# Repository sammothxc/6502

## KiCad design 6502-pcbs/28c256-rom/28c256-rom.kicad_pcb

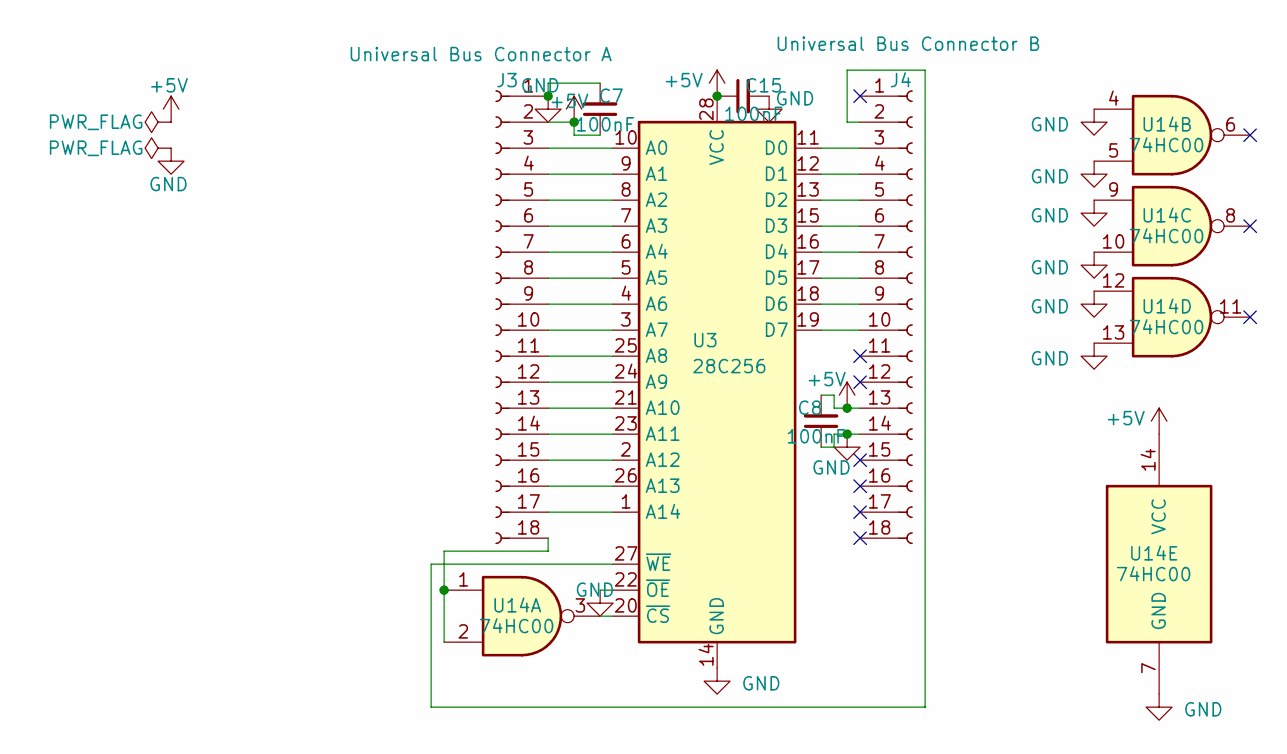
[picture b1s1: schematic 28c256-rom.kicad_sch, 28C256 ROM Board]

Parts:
C7, C8, C15: 100nF; C_Rect_L4.6mm_W2.0mm_P2.50mm_MKS02_FKP02
J3: Universal Bus Connector A; PinSocket_1x18_P2.54mm_Vertical
J4: Universal Bus Connector B; PinSocket_1x18_P2.54mm_Vertical
U3: 28C256; DIP-28_W15.24mm
U14: 74HC00; DIP-14_W7.62mm

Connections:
+5V: C7.1, C8.2, C15.1, J3.2, J4.13, U3.28 (VCC), U14.14 (VCC)
GND: C7.2, C8.1, C15.2, J3.1, J4.14, U3.14 (GND), U3.22 (~OE), U14.4, U14.5, U14.7 (GND), U14.9, U14.10, U14.12, U14.13
unnamed: J3.3, U3.10 (A0)
unnamed: J3.4, U3.9 (A1)
unnamed: J3.5, U3.8 (A2)
unnamed: J3.6, U3.7 (A3)
unnamed: J3.7, U3.6 (A4)
unnamed: J3.8, U3.5 (A5)
unnamed: J3.9, U3.4 (A6)
unnamed: J3.10, U3.3 (A7)
unnamed: J3.11, U3.25 (A8)
unnamed: J3.12, U3.24 (A9)
unnamed: J3.13, U3.21 (A10)
unnamed: J3.14, U3.23 (A11)
unnamed: J3.15, U3.2 (A12)
unnamed: J3.16, U3.26 (A13)
unnamed: J3.17, U3.1 (A14)
unnamed: J3.18, U14.1, U14.2
unnamed: J4.2, U3.27 (~WE)
unnamed: J4.3, U3.11 (D0)
unnamed: J4.4, U3.12 (D1)
unnamed: J4.5, U3.13 (D2)
unnamed: J4.6, U3.15 (D3)
unnamed: J4.7, U3.16 (D4)
unnamed: J4.8, U3.17 (D5)
unnamed: J4.9, U3.18 (D6)
unnamed: J4.10, U3.19 (D7)
unnamed: U3.20 (~CS), U14.3

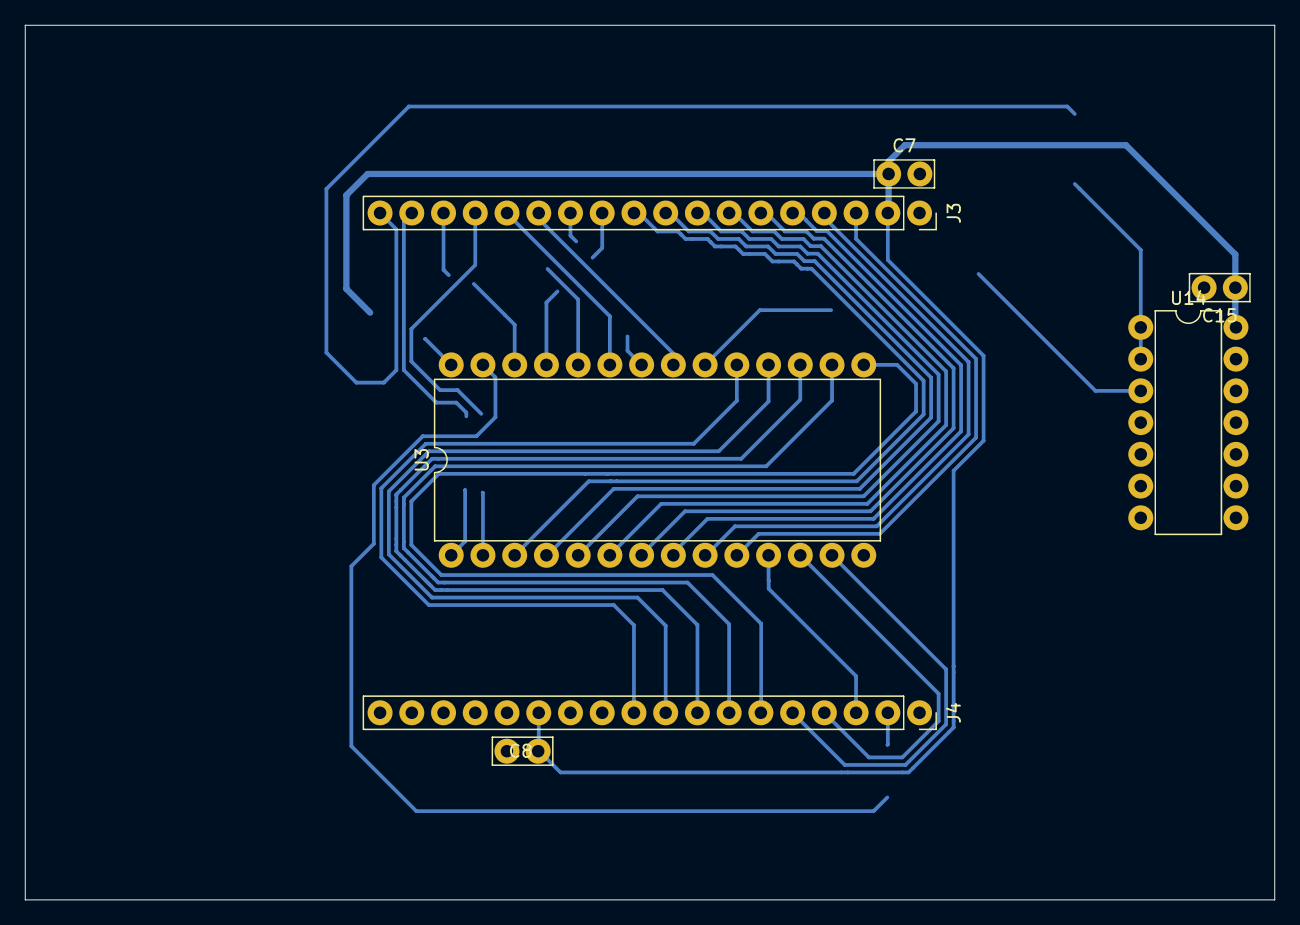
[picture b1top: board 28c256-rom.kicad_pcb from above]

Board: 2 copper layers, 100.0 x 70.0 mm, 7 parts (0 on the bottom side), 28 nets.

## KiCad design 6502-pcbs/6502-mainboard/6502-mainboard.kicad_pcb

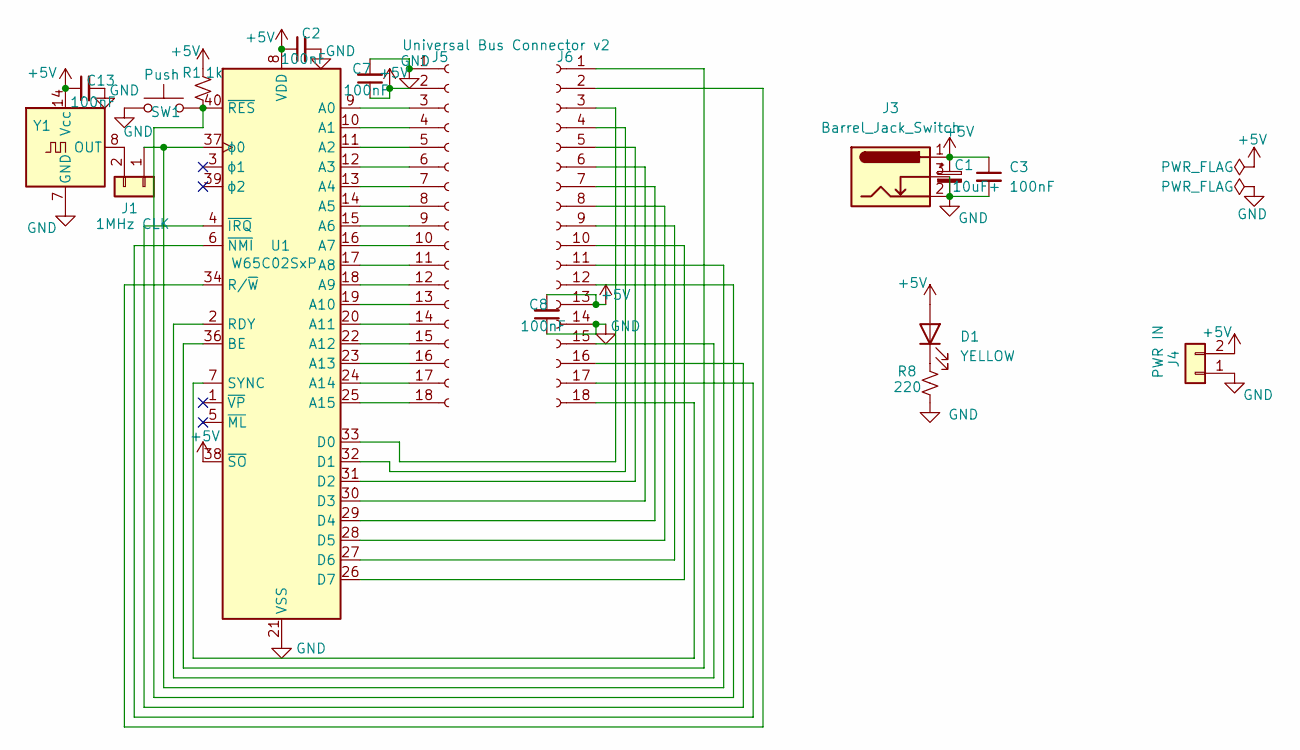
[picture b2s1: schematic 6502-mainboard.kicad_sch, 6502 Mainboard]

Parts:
C1: 10uF+; CP_Radial_D7.5mm_P2.50mm
C2, C3, C7, C8, C13: 100nF; C_Rect_L4.6mm_W2.0mm_P2.50mm_MKS02_FKP02
D1: YELLOW; LED_D5.0mm
J1: 1MHz CLK; PinHeader_1x02_P2.54mm_Vertical
J3: Barrel_Jack_Switch; BarrelJack_Kycon_KLDX-0202-xC_Horizontal
J4: PWR IN; PinSocket_1x02_P2.54mm_Vertical
J5, J6: Universal Bus Connector v2; PinSocket_1x18_P2.54mm_Vertical
R1: 1k; R_Axial_DIN0207_L6.3mm_D2.5mm_P10.16mm_Horizontal
R8: 220; R_Axial_DIN0207_L6.3mm_D2.5mm_P10.16mm_Horizontal
SW1: Push; SW_PUSH_6mm
U1: W65C02SxP; DIP-40_W15.24mm
Y1: ACO-xxxMHz; Oscillator_DIP-14

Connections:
+5V: C1.1, C2.1, C3.1, C7.1, C8.2, C13.1, D1.2 (A), J3.1, J4.2, J5.2, J6.13, R1.1, U1.8 (VDD), U1.38 (~SO), Y1.14 (Vcc)
GND: C1.2, C2.2, C3.2, C7.2, C8.1, C13.2, J3.2, J3.3, J4.1, J5.1, J6.14, R8.2, SW1.1, U1.21 (VSS), Y1.7 (GND)
unnamed: D1.1 (K), R8.1
unnamed: J1.1, J6.11, U1.37 (ϕ0)
unnamed: J1.2, Y1.8 (OUT)
unnamed: J5.3, U1.9 (A0)
unnamed: J5.4, U1.10 (A1)
unnamed: J5.5, U1.11 (A2)
unnamed: J5.6, U1.12 (A3)
unnamed: J5.7, U1.13 (A4)
unnamed: J5.8, U1.14 (A5)
unnamed: J5.9, U1.15 (A6)
unnamed: J5.10, U1.16 (A7)
unnamed: J5.11, U1.17 (A8)
unnamed: J5.12, U1.18 (A9)
unnamed: J5.13, U1.19 (A10)
unnamed: J5.14, U1.20 (A11)
unnamed: J5.15, U1.22 (A12)
unnamed: J5.16, U1.23 (A13)
unnamed: J5.17, U1.24 (A14)
unnamed: J5.18, U1.25 (A15)
unnamed: J6.1, U1.36 (BE)
unnamed: J6.2, U1.34 (R/~W)
unnamed: J6.3, U1.33 (D0)
unnamed: J6.4, U1.32 (D1)
unnamed: J6.5, U1.31 (D2)
unnamed: J6.6, U1.30 (D3)
unnamed: J6.7, U1.29 (D4)
unnamed: J6.8, U1.28 (D5)
unnamed: J6.9, U1.27 (D6)
unnamed: J6.10, U1.26 (D7)
unnamed: J6.12, R1.2, SW1.2, U1.40 (~RES)
unnamed: J6.15, U1.2 (RDY)
unnamed: J6.16, U1.4 (~IRQ)
unnamed: J6.17, U1.6 (~NMI)
unnamed: J6.18, U1.7 (SYNC)

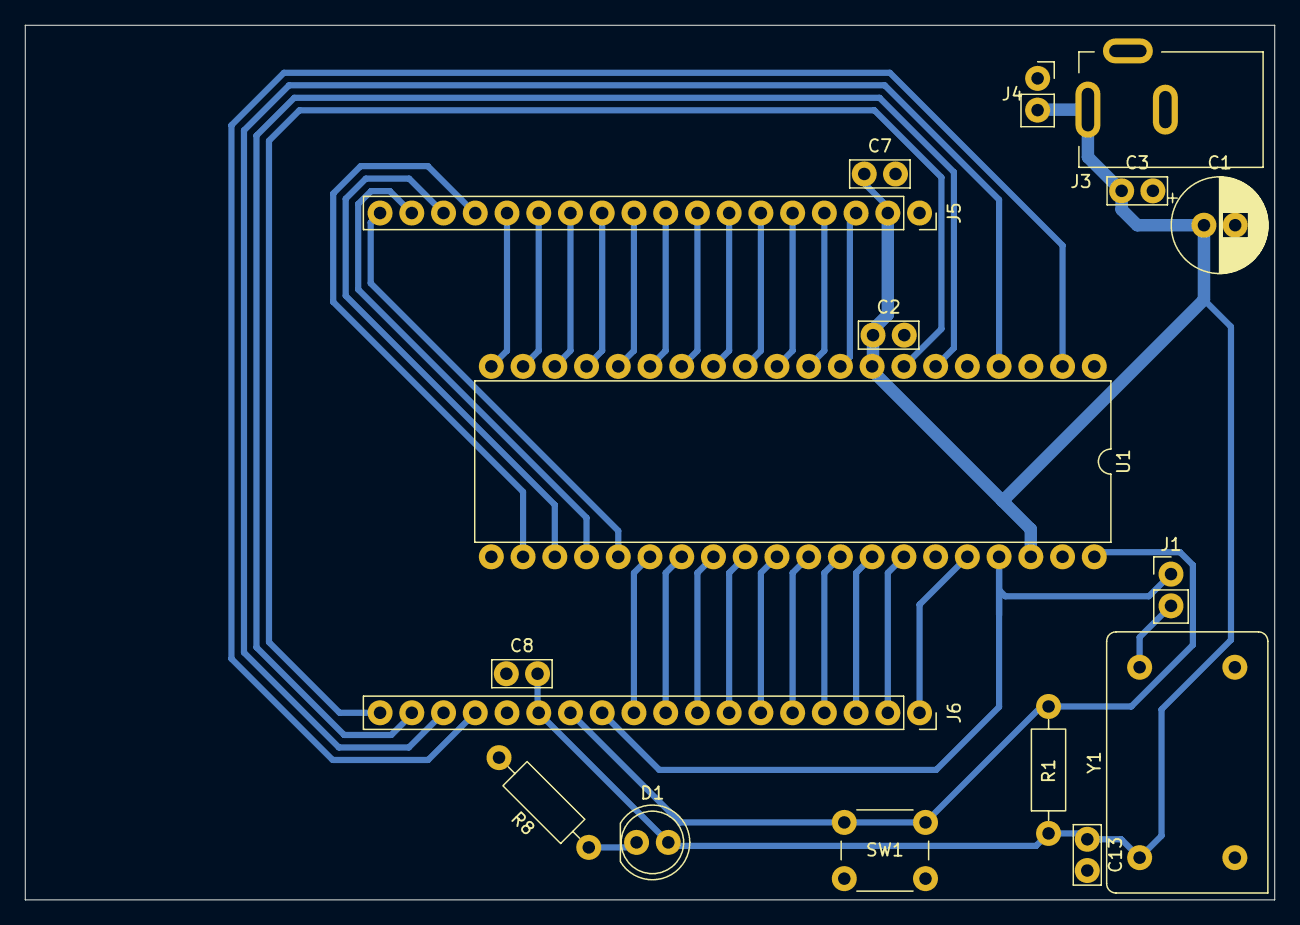
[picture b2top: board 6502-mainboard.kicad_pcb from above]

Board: 2 copper layers, 100.0 x 70.0 mm, 17 parts (0 on the bottom side), 36 nets.

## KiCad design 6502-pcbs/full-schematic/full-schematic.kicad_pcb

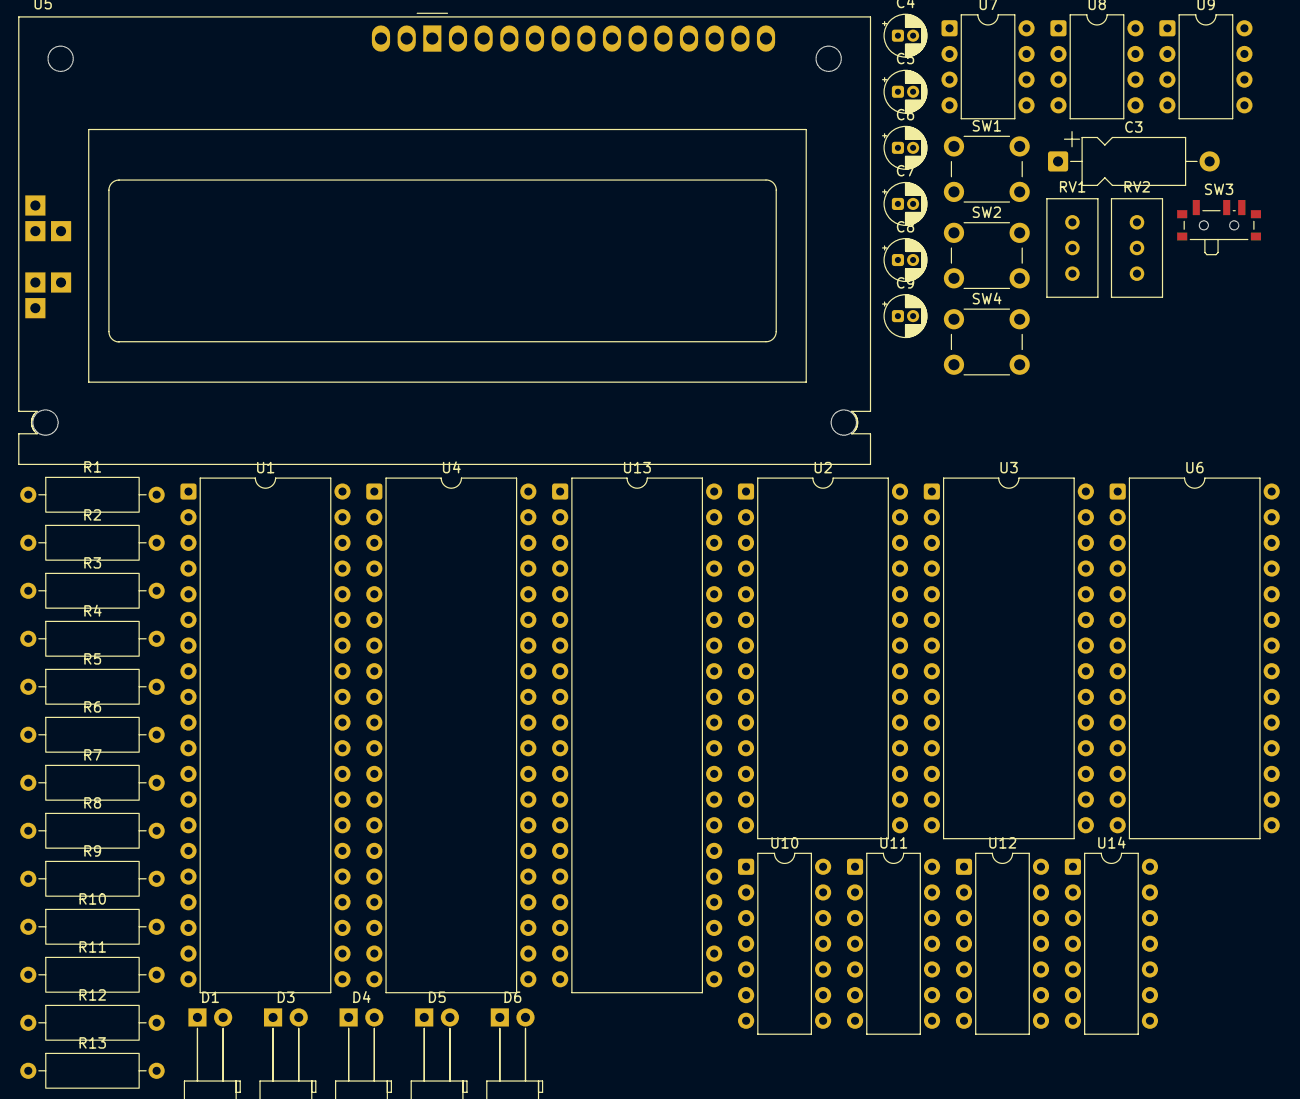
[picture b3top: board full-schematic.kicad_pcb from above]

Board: 2 copper layers, 45 parts (0 on the bottom side), 67 nets, no tracks yet.

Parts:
C3: 1uF; CP_Axial_L10.0mm_D4.5mm_P15.00mm_Horizontal
C4, C5, C8: 0.1uF; CP_Radial_D4.0mm_P1.50mm
C6, C7, C9: 0.01uF; CP_Radial_D4.0mm_P1.50mm
D1: RED; LED_D5.0mm_Horizontal_O6.35mm_Z9.0mm
D3, D4, D5, D6: YELLOW; LED_D5.0mm_Horizontal_O6.35mm_Z9.0mm
R1, R2, R3, R5, R6, R7, R12: 1k; R_Axial_DIN0309_L9.0mm_D3.2mm_P12.70mm_Horizontal
R4: 1M; R_Axial_DIN0309_L9.0mm_D3.2mm_P12.70mm_Horizontal
R8, R9, R10, R11, R13: 220; R_Axial_DIN0309_L9.0mm_D3.2mm_P12.70mm_Horizontal
RV1: 10k?; Potentiometer_Bourns_3386C_Horizontal
RV2: 1M; Potentiometer_Bourns_3386C_Horizontal
SW1, SW2, SW4: Push; SW_PUSH_6mm
SW3: SW_SPDT; SW_SPDT_PCM12
U1: W65C02SxP; DIP-40_W15.24mm
U2: HM62256BLP; DIP-28_W15.24mm
U3: 28C256; DIP-28_W15.24mm
U4: W65C22SxP; DIP-40_W15.24mm
U5: RC1602A
U6: W65C51NxP; DIP-28_W15.24mm
U7, U8, U9: NE555P; DIP-8_W7.62mm
U10: 74LS08; DIP-14_W7.62mm
U11: 74LS04; DIP-14_W7.62mm
U12: 74LS32; DIP-14_W7.62mm
U13: ATmega644-20P; DIP-40_W15.24mm
U14: 74HC00; DIP-14_W7.62mm

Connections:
+5V: C4.1, C5.1, R1.1, R2.1, R4.1, R5.1, R6.1, R7.1, R12.1, U1.2 (RDY), U1.4 (~IRQ), U1.6 (~NMI), U1.8 (VDD), U1.36 (BE), U1.38 (~SO), U2.28 (VCC), U3.27 (~WE), U3.28 (VCC), U4.20 (VCC), U5.2 (VDD), U5.15 (A/VEE), U7.4 (R), U7.8 (VCC), U8.4 (R), U8.8 (VCC), U9.8 (VCC), U13.10 (VCC), U13.30 (AVCC)
/HALT: D6.2 (A), U11.3, U13.14 (PD0)
GND: C3.2, C4.2, C5.2, C6.2, C7.2, C8.2, C9.2, R8.2, R9.2, R10.2, R11.2, R13.2, RV1.3, SW1.1, SW2.1, SW4.1, U1.21 (VSS), U2.14 (GND), U3.14 (GND), U3.22 (~OE), U4.1 (VSS), U5.1 (VSS), U5.16 (K), U6.1 (VSS_1), U7.1 (GND), U8.1 (GND), U9.1 (GND), U9.6 (THR), U13.11 (GND), U13.31 (GND)
unnamed: D1.2 (A), U1.37 (ϕ0), U10.8, U11.5, U13.16 (PD2)
unnamed: D1.1 (K), R8.1
unnamed: D3.2 (A), U8.3 (Q), U10.5
unnamed: D3.1 (K), R9.1
unnamed: D4.2 (A), U7.3 (Q), U10.1
unnamed: D4.1 (K), R10.1
unnamed: D5.2 (A), U9.3 (Q), U10.2, U11.1
unnamed: D5.1 (K), R11.1
unnamed: D6.1 (K), R13.1
unnamed: R3.2, RV2.2
unnamed: R6.2, SW3.1 (A), U9.2 (TR)
unnamed: R7.2, SW3.3 (C), U9.4 (R)
unnamed: U1.9 (A0), U2.10 (A0), U3.10 (A0), U13.40 (PA0)
unnamed: U1.10 (A1), U2.9 (A1), U3.9 (A1), U13.39 (PA1)
unnamed: U1.11 (A2), U2.8 (A2), U3.8 (A2), U13.38 (PA2)
unnamed: U1.12 (A3), U2.7 (A3), U3.7 (A3), U13.37 (PA3)
unnamed: U1.13 (A4), U2.6 (A4), U3.6 (A4), U13.36 (PA4)
unnamed: U1.14 (A5), U2.5 (A5), U3.5 (A5), U13.35 (PA5)
unnamed: U1.15 (A6), U2.4 (A6), U3.4 (A6), U13.34 (PA6)
unnamed: U1.16 (A7), U2.3 (A7), U3.3 (A7), U13.33 (PA7)
unnamed: U1.17 (A8), U2.25 (A8), U3.25 (A8), U13.1 (PB0)
unnamed: U1.18 (A9), U2.24 (A9), U3.24 (A9), U13.2 (PB1)
unnamed: U1.19 (A10), U2.21 (A10), U3.21 (A10), U13.3 (PB2)
unnamed: U1.20 (A11), U2.23 (A11), U3.23 (A11), U13.4 (PB3)
unnamed: U1.22 (A12), U2.2 (A12), U3.2 (A12), U13.5 (PB4)
unnamed: U1.23 (A13), U2.26 (A13), U3.26 (A13), U13.6 (PB5)
unnamed: U1.24 (A14), U2.1 (A14), U3.1 (A14), U13.7 (PB6)
unnamed: U1.25 (A15), U13.8 (PB7), U14.1, U14.2
unnamed: U1.33 (D0), U2.11 (Q0), U3.11 (D0), U4.33 (D0), U13.22 (PC0)
unnamed: U1.32 (D1), U2.12 (Q1), U3.12 (D1), U4.32 (D1), U13.23 (PC1)
unnamed: U1.31 (D2), U2.13 (Q2), U3.13 (D2), U4.31 (D2), U13.24 (PC2)
unnamed: U1.30 (D3), U2.15 (Q3), U3.15 (D3), U4.30 (D3), U13.25 (PC3)
unnamed: U1.29 (D4), U2.16 (Q4), U3.16 (D4), U4.29 (D4), U13.26 (PC4)
unnamed: U1.28 (D5), U2.17 (Q5), U3.17 (D5), U4.28 (D5), U13.27 (PC5)
unnamed: U1.27 (D6), U2.18 (Q6), U3.18 (D6), U4.27 (D6), U13.28 (PC6)
unnamed: U1.26 (D7), U2.19 (Q7), U3.19 (D7), U4.26 (D7), U13.29 (PC7)
unnamed: U1.34 (R/~W), U13.15 (PD1)
unnamed: R1.2, SW1.2, U1.40 (~RES)
unnamed: U3.20 (~CS), U14.3
unnamed: U4.7 (PA5), U5.4 (RS)
unnamed: U4.8 (PA6), U5.5 (R/W)
unnamed: U4.9 (PA7), U5.6 (E)
unnamed: U4.10 (PB0), U5.7 (DB0)
unnamed: U4.11 (PB1), U5.8 (DB1)
unnamed: U4.12 (PB2), U5.9 (DB2)
unnamed: U4.13 (PB3), U5.10 (DB3)
unnamed: U4.14 (PB4), U5.11 (DB4)
unnamed: U4.15 (PB5), U5.12 (DB5)
unnamed: U4.16 (PB6), U5.13 (DB6)
unnamed: U4.17 (PB7), U5.14 (DB7)
unnamed: RV1.2, U5.3 (VO)
unnamed: C6.1, U7.5 (CV)
unnamed: R2.2, R3.1, U7.7 (DIS)
unnamed: C3.1, RV2.3, U7.2 (TR), U7.6 (THR)
unnamed: C7.1, U8.5 (CV)
unnamed: C8.1, R4.2, U8.6 (THR), U8.7 (DIS)
unnamed: R5.2, SW2.2, U8.2 (TR)
unnamed: C9.1, U9.5 (CV)
unnamed: U10.3, U12.1
unnamed: U10.4, U11.2
unnamed: U10.6, U12.2
unnamed: U10.9, U12.3
unnamed: U10.10, U11.4
unnamed: R12.2, SW4.2, U13.9 (~RESET)

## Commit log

2025-07-14 makerom.py
2025-07-14 flashrom.py, and eeprom programmer stuff
2025-07-14 flashrom work
2025-07-14 arduino prorgammer
2025-07-15 mega2560
2025-08-01 msbasic
2025-08-04 rom2
2025-08-04 makerom v2
2025-08-04 fixes
2025-08-07 mega2560 programmer
2025-08-07 assembly
2025-08-12 Add LCD Hello World example and related resources
    Replaced the original helloworld.asm with a new 65C02 assembly example for displaying 'Hello, World!' on an LCD. Added the corresponding binary, datasheets for relevant components (74HC00, HD44780, H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
2025-08-14 Normalize line endings in project files
    Converted line endings from LF to CRLF in .gitignore, LICENSE, and source files to ensure consistency across platforms. No functional changes were made to the code or license text.
2025-09-17 more progs
2025-11-11 pcbs
2025-11-11 kicad stuff
2025-11-12 initial 6502 schematic
2025-11-12 datasheets and bus timing
2025-11-13 even more pcb
2025-11-13 daughterboard boilerplate files
2025-11-13 555-clock
2025-11-14 6502 mainboard
2025-11-14 .gitignore stuff
2025-11-14 28c256 rom
2025-11-14 28c256 rom pcb
